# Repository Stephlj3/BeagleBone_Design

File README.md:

# project-template

This repository can be forked for each new project.  This structure has a few goals:
* Standardization of project structure
* Making it trivially easy to distinguish human changes vs. automated outputs
* Tracking hardware bugs and bringup problems in a sensible way

## Description of Folders
* human/   Human modified files.  Many of these will be copies from the bot/ directory with light modification.
  * doc/  Human documentation relevant to the project.
  * input/  The design generator fed in to JITPCB, generated by human.  Also contains a makefile which will populate the bot/ directory.
  * xxxxx/ Copies of folders from the "bot" directory with human modifications.
* bot/ This folder should contain files generated only by a pure pipeline through the tool from the inputspec.
  * esir/ All passes of esir files
  * fab/ gerbers, ncdrill, bom.
  * kicad/ Kicad export.
  
## New Project Process
* Click the 'Use this template' button, set up the repo and clone it.
* Make sure that the stanza.proj file in human/input includes points to the libraries you need (e.g. ocdb)
* Using your (presumably) human brain, write the design generator in human/input.
* Generate your design by running the REPL from the human/input directory
* If JITPCB's outputs do not meet your requirements, copy the outputs from the bot directory (esir, kicad) to the human directory and make modifications in the human directory. 

## Release and Bringup Process
* When you are ready to release a design to fabrication, create a new dated folder in the releases/ dir.  Date format should be YYYYMMDD.
* Make sure all your changes are committed to git.
* Copy the "human" and "bot" folders in to the dated folder in release.
* If you zip a subset of files (eg just the kicad files) to send to the customer or fab house, add the zip file as well in the dated directory.

# Reverse flow usage
When you are finalizing schematics: 
1. Build the generator in the human/input directory, using export-kicad
2. Check the generated schematic file and jitpcb-associations file into the repository
3. Ensure that `export-kicad` is going to use your existing schematic by setting in the list of arguements:
```
  `fresh => false 
```
4. Make changes to the schematic, save them, and check them into the repository
5. When you make a change to the generator, re-run the generator in the input directory. **It will overwrite your kicad project, keeping as many of your saved schematic edits as possible.**
6. If something goes wrong, restore the schematic using git.

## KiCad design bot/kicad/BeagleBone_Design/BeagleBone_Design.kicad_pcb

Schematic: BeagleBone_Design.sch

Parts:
C0, C1, C4, C5, C6, C7, C8, C9, C10, C15, C17, C18, C19, C20, C34, C49, C50, C68, C88, C89, C137, C148: 10.0μF; ipc-two-pin-package$81; Tolerance 0.002%; Maximum Voltage UNKNOWNV
C2: 22.0μF; ipc-two-pin-package$81; Tolerance 0.002%; Maximum Voltage UNKNOWNV
C3, C21, C22, C23, C24, C25, C26, C27, C28, C29, C30, C31, C32, C33, C35, C36, C37, C41, C42, C43, C48, C51, C52, C53, C54, C55, C56, C57, C58, C59, C60, C61, C62, C63, C64, C65, C66, C67, C69, C70, C71, C72, C73, C74, C75, C76, C77, C78, C79, C80, C81, C82, C83, C84, C86, C90, C91, C92, C93, C94, C95, C96, C97, C98, C99, C100, C101, C102, C103, C105, C107, C109, C111, C119, C120, C121, C122, C123, C124, C126, C128, C130, C132, C134, C135, C136, C140, C143, C145, C147, C149, C170, C171: 100.0nF; ipc-two-pin-package$81; Tolerance 0.002%; Maximum Voltage UNKNOWNV
C11, C14, C16, C113: 4.7μF; ipc-two-pin-package$81; Tolerance 0.002%; Maximum Voltage UNKNOWNV
C12, C13, C106, C108, C125, C127, C129, C131, C144: 2.2μF; ipc-two-pin-package$81; Tolerance 0.002%; Maximum Voltage UNKNOWNV
C38, C39, C40, C87, C110, C112, C139: 1.0μF; ipc-two-pin-package$81; Tolerance 0.002%; Maximum Voltage UNKNOWNV
C44, C45, C46: 100.0mF; ipc-two-pin-package$81; Tolerance 0.002%; Maximum Voltage UNKNOWNV
C47: 1.0F; ipc-two-pin-package$81; Tolerance 0.002%; Maximum Voltage UNKNOWNV
C85, C104: 1.0nF; ipc-two-pin-package$81; Tolerance 0.002%; Maximum Voltage UNKNOWNV
C114, C138: 470.0pF; ipc-two-pin-package$81; Tolerance 0.002%; Maximum Voltage UNKNOWNV
C115, C116, C166, C167, C168, C169: 15.0pF; ipc-two-pin-package$81; Tolerance 0.002%; Maximum Voltage UNKNOWNV
C117, C118, C141, C142: 26.0pF; ipc-two-pin-package$81; Tolerance 0.002%; Maximum Voltage UNKNOWNV
C133: 10.0nF; ipc-two-pin-package$81; Tolerance 0.002%; Maximum Voltage UNKNOWNV
C146: 100.0μF; ipc-two-pin-package$81; Tolerance 0.002%; Maximum Voltage UNKNOWNV
C150, C151, C152, C153, C154, C155, C156, C157, C158, C159, C160, C161, C162, C163, C164, C165: 47.0pF; ipc-two-pin-package$81; Tolerance 0.002%; Maximum Voltage UNKNOWNV
D0, D1, D2, D3, D4: LTST-C191TBKT; ipc-two-pin-package$340
D5: RB751V40,115; two-pin-package$403
F0: RXEF010; footprint$62
FB0, FB1, FB2, FB3, FB4, FB5: LI0805H151R-10; ipc-two-pin-package$195
J0: UX60SC-MB-5ST(80); usb_5Ffootprint
J1: 87520-0010BLF; usb-87520-0010BLF-package
J2: PJ-002AH; footprint$53
J3: 10118241-001RLF; hdmi-10118241-001RLF-package
J4: 7499010211A; eth_5Ffootprint
J5: 2201778-1; usd-2201778-1-package
J6, J7: PPPC232LFBN-RC; p46_5Ffootprint
J8: RSM-110-02-S-D; RSM-110-02-S-D_5Ffootprint
J9: 68000-406HLF; _5F68000-406HLF_5Ffootprint
L0, L1, L2: LQM2HPN2R2MG0L; ind_5Ffootprint
Q0, Q1, Q2, Q3: DMN26D0UT-7; SOT-523
R0, R1, R67, R69, R71, R73, R113, R123, R124, R125, R126, R127, R128, R129, R130, R131, R132, R133, R134, R135, R136, R137, R138, R139, R140, R141, R142, R143, R144, R145, R146, R147, R148, R149, R150, R151, R152, R153, R154: 100.0kΩ; ipc-two-pin-package$81; Tolerance 0.02%
R2, R42, R43, R44, R45, R46, R47, R82, R83, R94, R95, R96, R99: 1.5kΩ; ipc-two-pin-package$81; Tolerance 0.02%
R3, R6, R9, R10, R12, R24, R25, R34, R35, R48, R52, R53, R54, R55, R56, R57, R58, R59, R81, R90, R91, R92, R93, R97: 10.0kΩ; ipc-two-pin-package$81; Tolerance 0.02%
R4, R30, R31, R32, R33: 49.9Ω; ipc-two-pin-package$81; Tolerance 0.02%
R5, R26, R37, R38, R39, R40, R49, R50, R60, R62, R63, R65, R76, R77, R78, R79, R89, R98, R111, R112, R117, R118, R119, R120, R121, R122: 0.0Ω; ipc-two-pin-package$81; Tolerance 0.02%
R7, R41, R66, R68, R70, R72, R74, R75, R114, R115, R116: 4.75kΩ; ipc-two-pin-package$81; Tolerance 0.02%
R8: 240.0Ω; ipc-two-pin-package$81; Tolerance 0.02%
R11, R13, R14, R15, R16, R17, R18, R19, R20: 50.0kΩ; ipc-two-pin-package$81; Tolerance 0.02%
R21, R80: 22.0Ω; ipc-two-pin-package$81; Tolerance 0.02%
R22: 280.0kΩ; ipc-two-pin-package$81; Tolerance 0.02%
R23: 470.0kΩ; ipc-two-pin-package$81; Tolerance 0.02%
R27, R28: 470.0Ω; ipc-two-pin-package$81; Tolerance 0.02%
R29: 12.1kΩ; ipc-two-pin-package$81; Tolerance 0.02%
R36: 1.0Ω; ipc-two-pin-package$81; Tolerance 0.02%
R51: 100.0mΩ; ipc-two-pin-package$81; Tolerance 0.02%
R61, R64, R88: 1.0MΩ; ipc-two-pin-package$81; Tolerance 0.02%
R84, R85, R110: 33.0Ω; ipc-two-pin-package$81; Tolerance 0.02%
R86: 27.0kΩ; ipc-two-pin-package$81; Tolerance 0.02%
R87: 10.0Ω; ipc-two-pin-package$81; Tolerance 0.02%
R100, R101, R102, R103, R104, R105, R106, R107, R108, R109, R155: 100.0Ω; ipc-two-pin-package$81; Tolerance 0.02%
S0, S1, S2: KMR231GLFS; footprint$17
U0: TPS65217xxx; qfn-package$74
U1: AM3358BZCZ100; bga-pkg$111
U2: MT41K256M16TW-107 IT:P; bga-pkg$282
U3: MTFC8GAKAJCN-4M-IT; bga-pkg$307
U4: TL5209DR; footprint$12
U5, U6: TPD4S012DRYR; uson-dry0006a
U7: TPS2051D; footprint$40
U8: SN74LVC1G07DCK; dck-R-PDSO-G5
U9: SN74LVC1G06DCK; dck-R-PDSO-G5
U10: SN74LVC2G241DCU; dcu-S-PDSO-G8
U11, U12: TPD4E02B04DQAR; footprint$59
U13: TPD4E05U06QDQARQ1; footprint$65
U14: TDA19988BHN/C1,557; QFN64_5FWITHTHERMALPAD
U15: SN74AUC1G74DCT; sm8-package$406
U16: LAN8710A-EZC-TR; QFN32_5FWITHTHERMALPAD
U17: 24LC32AT-I/OT; SOT-23-5-package
Y0: CM200C32768AZFT; xtal_5Ffootprint
Y1: 445C33D24M00000; SMD-2$350
Y2: ASDMB-24.576MHZ-LC-T; SDMB-24-576MHZ-package
Y3: 445C33D25M00000; SMD-2$350

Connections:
AIN0: J7.39, U1.B6 (ain0)
AIN1: J7.40, U1.C7 (ain1)
AIN2: J7.37, U1.B7 (ain2)
AIN3: J7.38, U1.A7 (ain3)
AIN4: J7.33, U1.C8 (ain4)
AIN5: J7.36, U1.B8 (ain5)
AIN6: J7.35, U1.A8 (ain6)
AIN7: R74.2, R75.2, U1.C9 (ain7)
BF_IN: U1.R14 (io36), U9.2 (a)
B_UART0_RX: J9.4, R113.2, U10.2 (a1)
B_UART0_TX: J9.5, U10.3 (y2)
CLKOUT2: J7.41, J8.18, R119.2, R120.2
CLKOUT_SRC: R119.1, U1.D14 (io1)
CPU_vdd_pll: C44.1, C45.1, C46.1, C47.1, FB0.2, U1.E7 (VDDS_PLL_DDR), U1.H15 (VDDS_PLL_MPU), U1.R10 (VDDS_PLL_CORE_LCD), U1.R11 (VDDS_OSC)
DDR3L_ZQ: R8.1, U2.L8 (pwr_zq)
DDR_A0: U1.F3 (acc_a0), U2.N3 (acc_a0)
DDR_A1: U1.H1 (acc_a1), U2.P7 (acc_a1)
DDR_A2: U1.E4 (acc_a2), U2.P3 (acc_a2)
DDR_A3: U1.C3 (acc_a3), U2.N2 (acc_a3)
DDR_A4: U1.C2 (acc_a4), U2.P8 (acc_a4)
DDR_A5: U1.B1 (acc_a5), U2.P2 (acc_a5)
DDR_A6: U1.D5 (acc_a6), U2.R8 (acc_a6)
DDR_A7: U1.E2 (acc_a7), U2.R2 (acc_a7)
DDR_A8: U1.D4 (acc_a8), U2.T8 (acc_a8)
DDR_A9: U1.C1 (acc_a9), U2.R3 (acc_a9)
DDR_A10: U1.F4 (acc_a10), U2.L7 (acc_a10)
DDR_A11: U1.F2 (acc_a11), U2.R7 (acc_a11)
DDR_A12: U1.E3 (acc_a12), U2.N7 (acc_a12)
DDR_A13: U1.H3 (acc_a13), U2.T3 (acc_a13)
DDR_A14: U1.H4 (acc_a14), U2.T7 (acc_a14)
DDR_BA0: U1.C4 (acc_ba0), U2.M2 (acc_ba0)
DDR_BA1: U1.E1 (acc_ba1), U2.N8 (acc_ba1)
DDR_BA2: U1.B3 (acc_ba2), U2.M3 (acc_ba2)
DDR_CASn: U1.F1 (acc_nCAS), U2.K3 (acc_nCAS)
DDR_CKE: R3.1, U1.G3 (acc_cke), U2.K9 (acc_cke)
DDR_CLK: U1.D2 (acc_ck_P), U2.J7 (acc_ck_P)
DDR_CLKn: U1.D1 (acc_ck_N), U2.K7 (acc_ck_N)
DDR_CSn: U1.H2 (acc_nCS), U2.L2 (acc_nCS)
DDR_D0: U1.M3 (dat_dq0), U2.E3 (dat_dq0)
DDR_D1: U1.M4 (dat_dq1), U2.F7 (dat_dq1)
DDR_D2: U1.N1 (dat_dq2), U2.F2 (dat_dq2)
DDR_D3: U1.N2 (dat_dq3), U2.F8 (dat_dq3)
DDR_D4: U1.N3 (dat_dq4), U2.H3 (dat_dq4)
DDR_D5: U1.N4 (dat_dq5), U2.H8 (dat_dq5)
DDR_D6: U1.P3 (dat_dq6), U2.G2 (dat_dq6)
DDR_D7: U1.P4 (dat_dq7), U2.H7 (dat_dq7)
DDR_D8: U1.J1 (dat_dq8), U2.D7 (dat_dq8)
DDR_D9: U1.K1 (dat_dq9), U2.C3 (dat_dq9)
DDR_D10: U1.K2 (dat_dq10), U2.C8 (dat_dq10)
DDR_D11: U1.K3 (dat_dq11), U2.C2 (dat_dq11)
DDR_D12: U1.K4 (dat_dq12), U2.A7 (dat_dq12)
DDR_D13: U1.L3 (dat_dq13), U2.A2 (dat_dq13)
DDR_D14: U1.L4 (dat_dq14), U2.B8 (dat_dq14)
DDR_D15: U1.M1 (dat_dq15), U2.A3 (dat_dq15)
DDR_DQM0: U1.M2 (dat_dm0), U2.E7 (dat_dm0)
DDR_DQM1: U1.J2 (dat_dm1), U2.D3 (dat_dm1)
DDR_DQS0: U1.P1 (dat_dqs0_P), U2.F3 (dat_dqs0_P)
DDR_DQS1: U1.L1 (dat_dqs1_P), U2.C7 (dat_dqs1_P)
DDR_DQSN0: U1.P2 (dat_dqs0_N), U2.G3 (dat_dqs0_N)
DDR_DQSN1: U1.L2 (dat_dqs1_N), U2.B7 (dat_dqs1_N)
DDR_ODT: U1.G1 (acc_odt), U2.K1 (acc_odt)
DDR_RASn: U1.G4 (acc_nRAS), U2.J3 (acc_nRAS)
DDR_RESETn: R2.1, U1.G2 (acc_nRESET), U2.T2 (acc_nRESET)
DDR_VREF: C57.1, C104.1, C105.1, R9.2, R10.1, U1.J4 (DDR_VREF), U2.H1 (pwr_vrefdq), U2.M8 (pwr_vrefca)
DDR_WEn: U1.B2 (acc_nWE), U2.L3 (acc_nWE)
DVI_+5V: F0.1, J3.19 (vcc_5v), R82.2, R83.2
EARTH_GND: J0.6 (shield1), J0.7 (shield2), J0.8 (shield3), J0.9 (shield4), J1.5 (shield1), J1.6 (shield2), J3.20 (mtg1), J3.21 (mtg2), J3.22 (mtg3), J3.23 (mtg4), J4.15 (shield1), J4.16 (shield2), J5.11 (gnd1), J5.12 (gnd2), J5.13 (gnd3), J5.14 (gnd4), J5.15 (gnd5), J5.16 (gnd6), R36.1
EHRPWM1A: J7.14, U1.U14 (io34)
EHRPWM1B: J7.16, U1.T14 (io35)
EHRPWM2A: J6.19, U1.U10 (io24)
EHRPWM2B: J6.13, U1.T10 (io25)
ETH_TXD4: R97.1, U16.18 (nINT_TXER_TXD4)
FF_Q: R85.1, U15.5 (q)
GNDA_ADC: C82.2, C83.2, C84.2, C85.2, FB2.2, J7.34, U1.A9 (VREFN), U1.E8 (VSSA_ADC)
GND_OSC0: C117.2, C118.2, R62.1, R65.2, U1.V11 (VSS_OSC)
GND_OSC1: C115.2, C116.2, R65.1, U1.A5 (VSS_RTC)
GPIO0_7: J7.42, R121.2, R122.2
GPIO0_7SRC: R121.1, U1.C18 (io67)
GPIO0_26: J6.14, U1.T11 (io26)
GPIO0_27: J6.17, U1.U12 (io27)
GPIO1_12: J6.12, U1.T12 (io28)
GPIO1_13: J6.11, U1.R12 (io29)
GPIO1_14: J6.16, U1.V13 (io30)
GPIO1_15: J6.15, U1.U13 (io31)
GPIO1_16: J7.15, R117.2, R118.2
GPIO1_17: J7.23, U1.V14 (io33)
GPIO1_28: J7.12, U1.U18 (io13)
GPIO1_29: J6.26, U1.V6 (io5)
GPIO2_1: J6.18, U1.V12 (io4)
GPIO3_18: R122.1, U1.B12 (io111)
GPIO3_19: J7.27, U1.C13 (io112)
GPIO3_20: R120.1, U1.D13 (io113)
GPIO3_21: J7.25, R84.2, U1.A14 (io106)
GRNA: J4.9 (grna), U16.3 (LED1_REGOFF)
HDMICLK_DISn: U1.V17 (io43)
HDMI_1V8: C124.1, C125.1, C126.1, C127.1, C128.1, C129.1, C130.1, C131.1, FB4.2, U14.5 (VDDC0-1V8), U14.14 (VDDIOA-1V8), U14.29 (VDDC1-1V8), U14.35 (VDDA0-1V8), U14.36 (VDDA1-TX-1V8), U14.41 (VDDA2-TX-1V8), U14.46 (VDDA3-TX-1V8), U14.47 (VDDA-PLL0-1V8), U14.48 (VDDA-PLL1-1V8), U14.55 (VDDIOB-1V8)
HDMI_12MHZ: R85.2, U14.27 (OSC_IN_AP3)
HDMI_CEC: D5.1 (c), J3.15 (cec), U13.4 (IO3), U14.30 (CEC)
HDMI_DSCL: J3.17 (scl), R82.1, U13.1 (IO1), U14.33 (DSCL)
HDMI_DSDA: J3.18 (sda), R83.1, U13.2 (IO2), U14.32 (DSDA)
HDMI_HPD: J3.1 (hplg), U13.5 (IO4), U14.31 (HPD)
HDMI_INT: R81.1, U1.U16 (io41), U14.50 (INT)
HDMI_TX0_N: J3.11 (dat0_n), U12.1 (IO1), U14.39 (TX0_N)
HDMI_TX0_P: J3.9 (dat0_p), U12.2 (IO2), U14.40 (TX0_P)
HDMI_TX1_N: J3.8 (dat1_n), U11.4 (IO3), U14.42 (TX1_N)
HDMI_TX1_P: J3.6 (dat1_p), U11.5 (IO4), U14.43 (TX1_P)
HDMI_TX2_N: J3.5 (dat2_n), U11.1 (IO1), U14.44 (TX2_N)
HDMI_TX2_P: J3.3 (dat2_p), U11.2 (IO2), U14.45 (TX2_P)
HDMI_TXC_N: J3.14 (clk_n), U12.4 (IO3), U14.37 (TXC_N)
HDMI_TXC_P: J3.12 (clk_p), U12.5 (IO4), U14.38 (TXC_P)
I2C0_SCL: R42.1, U0.28 (SCL), U1.C16 (io63), U14.52 (CSCL), U17.1 (scl)
I2C0_SDA: R43.1, U0.27 (SDA), U1.C17 (io64), U14.51 (CSDA), U17.3 (sda)
I2C1_SCL: J7.17, R44.1, U1.A16 (io53)
I2C1_SDA: J7.18, R45.1, U1.B16 (io52)
I2C2_SCL: J7.19, R46.1, U1.D17 (io62)
I2C2_SDA: J7.20, R47.1, U1.D18 (io61)
JTAG_EMU0: J8.13, R114.2, U1.C14 (io2)
JTAG_EMU1: J8.14, R116.2, U1.B14 (io3)
JTAG_TCK: J8.9, J8.11, U1.A12 (tck)
JTAG_TDI: J8.3, U1.B11 (tdi)
JTAG_TDO: J8.7, U1.A11 (tdo)
JTAG_TMS: J8.1, U1.C11 (tms)
JTAG_TRSTn: J8.2, R115.2, U1.B10 (ntrst)
LCDDE: R79.2, U1.R6 (io105)
LCDHSYNC: R78.2, U1.R5 (io104)
LCDPCLK: R80.2, U1.V5 (io102)
LCDVSYNC: R77.2, U1.U5 (io103)
LCD_DATA0: C150.1, J6.45, R133.1, R134.1, U1.R1 (io86), U14.15 (VPC3)
LCD_DATA1: C151.1, J6.46, R135.1, R136.1, U1.R2 (io87), U14.13 (VPC4)
LCD_DATA2: C152.1, J6.43, R123.1, R124.1, R155.1, U1.R3 (io88), U14.12 (VPC5)
LCD_DATA3: C153.1, J6.44, R125.1, R126.1, U1.R4 (io89), U14.11 (VPC6)
LCD_DATA4: C154.1, J6.41, R127.1, R128.1, U1.T1 (io90), U14.10 (VPC7)
LCD_DATA5: C155.1, J6.42, R129.1, R130.1, U1.T2 (io91), U14.7 (VPB2)
LCD_DATA6: C156.1, J6.39, R137.1, R138.1, U1.T3 (io92), U14.6 (VPB3)
LCD_DATA7: C157.1, J6.40, R139.1, R140.1, U1.T4 (io93), U14.3 (VPB4)
LCD_DATA8: C158.1, J6.37, R141.1, R142.1, U1.U1 (io94), U14.2 (VPB5)
LCD_DATA9: C159.1, J6.38, R143.1, R144.1, U1.U2 (io95), U14.1 (VPB6)
LCD_DATA10: C160.1, J6.36, R145.1, R146.1, U1.U3 (io96), U14.64 (VPB7)
LCD_DATA11: C161.1, J6.34, R147.1, R148.1, U1.U4 (io97), U14.60 (VPA3)
LCD_DATA12: C162.1, J6.35, R149.1, R150.1, U1.V2 (io98), U14.59 (VPA4)
LCD_DATA13: C163.1, J6.33, R151.1, R152.1, U1.V3 (io99), U14.58 (VPA5)
LCD_DATA14: C164.1, J6.31, R131.1, R132.1, U1.V4 (io100), U14.57 (VPA6)
LCD_DATA15: C165.1, J6.32, R153.1, R154.1, U1.T5 (io101), U14.56 (VPA7)
LCD_DE: J6.30, R79.1, U14.20 (DE-VREF)
LCD_HSYNC: J6.29, R78.1, U14.22 (HSYNC-VREF)
LCD_PCLK: J6.28, R80.1, U14.4 (PCLK)
LCD_VSYNC: J6.27, R77.1, U14.21 (VSYNC-VREF)
LDO_PGOOD: U0.46 (LDO_PGOOD), U1.B5 (RTC_PORZn)
LEDAA: D1.1 (a), R66.2
LEDBA: D2.1 (a), R68.2
LEDCA: D3.1 (a), R70.2
LEDDA: D4.1 (a), R72.2
LOOP_12M: U15.2 (d), U15.3 (qn)
MDIO_CLK: U1.M18 (io84), U16.17 (MDC)
MDIO_DATA: R99.2, U1.M17 (io85), U16.16 (MDIO)
MII1_COL: R108.1, U1.H16 (io75)
MII1_CRS_DV: R109.1, U1.H17 (io74)
MII1_REFCLK: R110.2, R111.1, R112.1
MII1_RXCLK: R105.1, U1.L18 (io76)
MII1_RXD0: R103.1, U1.M16 (io77)
MII1_RXD1: R102.1, U1.L15 (io78)
MII1_RXD2: R101.1, U1.L16 (io79)
MII1_RXD3: R100.1, U1.L17 (io80)
MII1_RXDV: R104.1, U1.J17 (io82)
MII1_RXERR: R106.1, U1.J15 (io81)
MII1_TXCLK: R107.1, U1.K18 (io68)
MII1_TXD0: U1.K17 (io69)
MII1_TXD1: U1.K16 (io70)
MII1_TXD2: U1.K15 (io71)
MII1_TXD3: U1.J18 (io72)
MII1_TXEN: U1.J16 (io73)
MMC0_CD: J5.9 (swa), J8.19, R53.2, U1.C15 (io54)
MMC0_CLKO: J5.5 (clk), R59.2, U1.G17 (io44)
MMC0_CMD: J5.3 (cmd), R58.2, U1.G18 (io45)
MMC0_DAT0: J5.7 (dat0), R54.2, U1.G16 (io46)
MMC0_DAT1: J5.8 (dat1), R55.2, U1.G15 (io47)
MMC0_DAT2: J5.1 (dat2), R56.2, U1.F18 (io48)
MMC0_DAT3: J5.2 (cd_dat3), R57.2, U1.F17 (io49)
MMC1_CLK: J6.21, R21.1, U1.U9 (io6)
MMC1_CMD: J6.20, R12.2, U1.V9 (io7), U3.M5 (dat_cmd)
MMC1_DAT0: J6.25, R13.2, U1.U7 (io16), U3.A3 (dat_d0)
MMC1_DAT1: J6.24, R14.2, U1.V7 (io17), U3.A4 (dat_d1)
MMC1_DAT2: J6.5, R15.2, U1.R8 (io18), U3.A5 (dat_d2)
MMC1_DAT3: J6.6, R16.2, U1.T8 (io19), U3.B2 (dat_d3)
MMC1_DAT4: J6.23, R17.2, U1.U8 (io20), U3.B3 (dat_d4)
MMC1_DAT5: J6.22, R18.2, U1.V8 (io21), U3.B4 (dat_d5)
MMC1_DAT6: J6.3, R19.2, U1.R9 (io22), U3.B5 (dat_d6)
MMC1_DAT7: J6.4, R20.2, U1.T9 (io23), U3.B6 (dat_d7)
MODE2: R94.1, R108.2, U16.15 (COL_CRS_DV_MODE2)
OSC0_IN: C117.1, R61.1, U1.V10 (OSC0_IN), Y1.1 (xtal1)
OSC0_OUT: R60.2, R61.2, U1.U11 (OSC0_OUT)
OSC1_IN: C115.1, R64.1, U1.A6 (OSC1_IN), Y0.1 (xtal1)
OSC1_OUT: R63.2, R64.2, U1.A4 (OSC1_OUT)
PHYX: C142.1, R87.1, Y3.2 (xtal2)
PHY_XTAL1: C141.1, R88.1, R89.1, Y3.1 (xtal1)
PHY_XTAL2: R87.2, R88.2, U16.4 (XTAL2)
PMIC_INT: R1.1, U0.45 (INT), U1.B18 (NNMI)
PMIC_ISET1: U0.35 (ISET1)
PMIC_ISET2: U0.36 (ISET2)
PMIC_PGOOD: U0.26 (PGOOD), U1.B15 (PORZn), U8.2 (a)
PMIC_POWR_EN: U0.9 (PWR_EN), U1.C6 (PMIC_POWER_EN)
PMIC_bypass: C4.1, U0.47 (BYPASS)
PMIC_int_ldo: C3.1, U0.48 (INT_LDO)
PMIC_sw1: L0.1, U0.20 (L1)
PMIC_sw2: L1.1, U0.23 (L2)
PMIC_sw3: L2.1, U0.31 (L3)
PROC_A15: U1.A15 (io0)
PWR_BUT: J7.9, S0.1 (p1), S0.3 (p3), U0.25 (PB_IN)
PWR_LEDR: D0.2 (c), R41.1
RCLKIN: R89.2, R112.2, U16.5 (XTAL1_CLKIN)
REFCLK0: R90.1, R105.2, R111.2, U16.7 (RXCLK_PHYAD1)
RXD0_MODE0: R96.1, R103.2, U16.11 (RXD0_MODE0)
RXD1_MODE1: R95.1, R102.2, U16.10 (RXD1_MODE1)
RXN: C169.1, J4.6 (rd_n), R33.1, U16.30 (RXN)
RXP: C168.1, J4.3 (rd_p), R32.1, U16.31 (RXP)
SDBOOT: R155.2, S2.1 (p1), S2.3 (p3)
SPI1_CS0: J7.28, U1.C12 (io110), U14.25 (AP1)
SPI1_D0: J7.29, U1.B13 (io108), U14.24 (AP0)
SPI1_D1: J7.30, U1.D12 (io109)
SPI1_SCLK: J7.31, U1.A13 (io107), U14.23 (ACLK)
SYS_5V: C2.1, C5.1, C7.1, C9.1, C11.1, C14.1, C16.1, C112.1, C119.1, C146.1, F0.2, J7.7, J7.8, R66.1, R68.1, R70.1, R72.1, U0.2 (VINLDO), U0.7 (SYS1), U0.8 (SYS2), U0.21 (VIN_DCDC1), U0.22 (VIN_DCDC2), U0.32 (VIN_DCDC3), U0.39 (LDO3_IN), U0.42 (LDO4_IN), U4.2 (IN), U7.2 (in1), U7.3 (in2)
SYS_RESETn: C144.1, C171.2, J7.10, J8.15, R48.1, S1.1 (p1), S1.3 (p3), U1.A10 (NRESET_INOUT), U8.4 (y), U16.19 (nRST)
TCT_RCT: C134.1, J4.4 (tct), J4.5 (rct), R98.1
TIMER4: J6.7, U1.R7 (io11)
TIMER5: J6.9, U1.T6 (io12)
TIMER6: J6.10, U1.U6 (io9)
TIMER7: J6.8, U1.T7 (io10)
TXN: C167.1, J4.2 (td_n), R31.1, U16.28 (TXN)
TXP: C166.1, J4.1 (td_p), R30.1, U16.29 (TXP)
U5_H18: R110.1, U1.H18 (io83)
U5_R13: R118.1, U1.R13 (io32)
U5_T13: R117.1, U1.T13 (io8)
UART0_RX: U1.E15 (io56), U10.6 (y1)
UART0_TX: U1.E16 (io55), U10.5 (a2)
UART1_RXD: J7.26, U1.D16 (io60)
UART1_TXD: J7.24, U1.D15 (io59)
UART2_RXD: J7.22, U1.A17 (io50)
UART2_TXD: J7.21, U1.B17 (io51)
UART4_RXD: J7.11, U1.T17 (io14)
UART4_TXD: J7.13, U1.U17 (io15)
USB0_DM: J0.2 (dm), U1.N18 (usb0_data_N), U5.2 (DM)
USB0_DP: J0.3 (dp), U1.N17 (usb0_data_P), U5.1 (DP)
USB0_ID: J0.4 (id), U1.P16 (USB0_ID), U5.3 (ID)
USB1_DM: J1.2 (dm), U1.R18 (usb1_data_N), U6.2 (DM)
USB1_DP: J1.3 (dp), U1.R17 (usb1_data_P), U6.1 (DP)
USB1_DRVVBUS: R52.1, U1.F15 (io66), U7.4 (en)
USB1_ID: R50.1, U1.P17 (USB1_ID)
USB1_OCn: R24.1, U1.T16 (io42), U7.5 (oc)
USB1_PWR: C120.1, C147.1, FB3.1, R51.2, U6.6 (VBUS), U7.6 (out3), U7.7 (out2), U7.8 (out1)
USB1_VBUS: R51.1, U1.T18 (USB1_VBUS)
USB_DC: C1.1, C145.1, J0.1 (vdd), R49.1, U0.12 (USB), U5.6 (VBUS)
USR0: Q0.2 (gate), R67.1, U1.V15 (io37)
USR1: Q1.2 (gate), R69.1, U1.U15 (io38)
USR2: Q2.2 (gate), R71.1, U1.T15 (io39)
USR3: Q3.2 (gate), R73.1, U1.V16 (io40)
VBUS: FB3.2, J1.1 (vbus)
VDDS: C77.1, C78.1, C79.1, C80.1, C81.1, R37.2, U1.E6 (VDDS1), U1.E14 (VDDS2), U1.F9 (VDDS3), U1.K13 (VDDS4), U1.N6 (VDDS5), U1.P9 (VDDS6), U1.P14 (VDDS7)
VDDS_DDR: C49.1, C50.1, C51.1, C52.1, C53.1, C54.1, C55.1, C56.1, C88.1, C89.1, C90.1, C91.1, C92.1, C93.1, C94.1, C95.1, C96.1, C97.1, C98.1, C99.1, C100.1, C101.1, C102.1, C103.1, R2.2, R9.1, R40.2, U1.E5 (VDDS_DDR1), U1.F5 (VDDS_DDR2), U1.G5 (VDDS_DDR3), U1.H5 (VDDS_DDR4), U1.J5 (VDDS_DDR5), U1.K5 (VDDS_DDR6), U1.L5 (VDDS_DDR7), U2.A1 (pwr_vddq0), U2.A8 (pwr_vddq5), U2.B2 (pwr_vdd2), U2.C1 (pwr_vddq1), U2.C9 (pwr_vddq6), U2.D2 (pwr_vddq3), U2.D9 (pwr_vdd6), U2.E9 (pwr_vddq7), U2.F1 (pwr_vddq2), U2.G7 (pwr_vdd4), U2.H2 (pwr_vddq4), U2.H9 (pwr_vddq8), U2.K2 (pwr_vdd3), U2.K8 (pwr_vdd5), U2.N1 (pwr_vdd0), U2.N9 (pwr_vdd7), U2.R1 (pwr_vdd1), U2.R9 (pwr_vdd8)
VDD_1V8: C15.1, C41.1, C42.1, C43.1, FB0.1, FB1.1, FB4.1, U0.40 (LDO3), U1.D10 (VDDS_SRAM_MPU_BB), U1.E9 (VDDS_SRAM_CORE_BG), U1.N16 (VDDA1P8V_USB0), U1.R16 (VDDA1P8V_USB1)
VDD_3V3A: C17.1, C48.1, C58.1, C59.1, C60.1, C61.1, C62.1, C63.1, C64.1, C65.1, C66.1, C67.1, C68.1, C69.1, C70.1, C71.1, C72.1, C73.1, C74.1, C75.1, C76.1, C122.1, C132.1, C133.1, C143.1, R24.2, R35.1, R42.2, R43.2, R44.2, R45.2, R46.2, R47.2, R48.2, R124.2, R126.2, R128.2, R130.2, R132.2, R134.2, R136.2, R138.2, R140.2, R142.2, R144.2, R146.2, R148.2, R150.2, R152.2, R154.2, U0.43 (LDO4), U1.E10 (VDDSHV61), U1.E11 (VDDSHV62), U1.E12 (VDDSHV63), U1.E13 (VDDSHV64), U1.F14 (VDDSHV65), U1.G14 (VDDSHV66), U1.H14 (VDDSHV41), U1.J14 (VDDSHV42), U1.K14 (VDDSHV51), U1.L14 (VDDSHV52), U1.N5 (VDDSHV67), U1.N15 (VDDA3P3V_USB0), U1.P5 (VDDSHV68), U1.P6 (VDDSHV69), U1.P7 (VDDSHV11), U1.P8 (VDDSHV12), U1.P10 (VDDSHV21), U1.P11 (VDDSHV22), U1.P12 (VDDSHV31), U1.P13 (VDDSHV32), U1.R15 (VDDA3P3V_USB1), U4.1 (EN), U9.5 (vcc), U15.6 (clrn), U15.7 (pren), U15.8 (vcc), U17.4 (vcc), Y2.4 (vdd)
VDD_3V3AUX: C13.1, D0.1 (a), U0.1 (VLDO2)
VDD_3V3B: C106.1, C107.1, C108.1, C109.1, C113.1, C123.1, C140.1, C148.1, C149.1, C170.2, FB5.1, J5.4 (vdd), J7.3, J7.4, J8.5, R11.1, R12.1, R13.1, R14.1, R15.1, R16.1, R17.1, R18.1, R19.1, R20.1, R22.1, R53.1, R54.1, R55.1, R56.1, R57.1, R58.1, R59.1, R74.1, R81.2, R86.1, R94.2, R95.2, R96.2, R99.1, R114.1, R116.1, U3.C6 (pwr_vccq0), U3.E6 (pwr_vcc0), U3.F5 (pwr_vcc1), U3.J10 (pwr_vcc2), U3.K9 (pwr_vcc3), U3.M4 (pwr_vccq1), U3.N4 (pwr_vccq2), U3.P3 (pwr_vccq3), U3.P5 (pwr_vccq4), U4.3 (OUT), U10.7 (oe_2), U10.8 (vcc), U16.12 (VDDIO)
VDD_5V: C0.1, J2.1 (VDD), J7.5, J7.6, U0.10 (AC)
VDD_ADC: C82.1, FB1.2, J7.32, R5.1, U1.D8 (VDDA_ADC)
VDD_CORE: C10.1, C18.1, C19.1, C20.1, C21.1, C22.1, C23.1, C24.1, C25.1, C26.1, C27.1, C28.1, C29.1, C30.1, C31.1, C32.1, C33.1, L2.2, U0.29 (VDCDC3), U1.F6 (VDD_CORE1), U1.F7 (VDD_CORE2), U1.G6 (VDD_CORE3), U1.G7 (VDD_CORE4), U1.G10 (VDD_CORE5), U1.H11 (VDD_CORE6), U1.J12 (VDD_CORE7), U1.K6 (VDD_CORE8), U1.K8 (VDD_CORE9), U1.K12 (VDD_CORE10), U1.L6 (VDD_CORE11), U1.L7 (VDD_CORE12), U1.L8 (VDD_CORE13), U1.L9 (VDD_CORE14), U1.M11 (VDD_CORE15), U1.M13 (VDD_CORE16), U1.N8 (VDD_CORE17), U1.N9 (VDD_CORE18), U1.N12 (VDD_CORE19), U1.N13 (VDD_CORE20)
VDD_MPU: C8.1, C34.1, C35.1, C36.1, C37.1, L1.2, U0.24 (VDCDC2), U1.F10 (VDD_MPU1), U1.F11 (VDD_MPU2), U1.F12 (VDD_MPU3), U1.F13 (VDD_MPU4), U1.G13 (VDD_MPU5), U1.H13 (VDD_MPU6), U1.J13 (VDD_MPU7)
VDD_PHYA: C135.1, C136.1, C137.1, FB5.2, R30.2, R31.2, R32.2, R33.2, R98.2, U16.1 (VDD2A), U16.27 (VDD1A)
VIO: C121.1, R0.2, R1.2, R39.2, U0.18 (VIO), U8.5 (vcc)
VRTC: C86.1, R7.2, R38.2, U1.D7 (VDDS_RTC)
WAKEUP: R0.1, R7.1, U0.13 (WAKEUP), U1.C5 (EXT_WAKEUP)
XDMA_EVENT_INTRO: J8.17, U15.1 (clk)
XTAL0_OUT: C118.1, R60.1, Y1.2 (xtal2)
XTAL1_OUT: C116.1, R63.1, Y0.4 (xtal2)
Y4_CLK: R84.1, Y2.3 (output)
YELA: J4.12 (yela), R34.1, U16.2 (LED2_nINTSEL)
eMMC_RSTn: R11.2, R76.1, U3.K5 (nRESET)
net_BUFFER_Y: R76.2, U9.4 (y)
net_CPU_USB0_CE: U1.M15 (USB0_CE)
net_CPU_USB0_VBUS: R49.2, U1.P15 (USB0_VBUS)
net_CPU_USB1_CE: U1.P18 (USB1_CE)
net_CPU_cpu_CAP_VBB_MPU: C40.1, U1.C10 (CAP_VBB_MPU)
net_CPU_cpu_CAP_VDD_RTC: C87.1, U1.D6 (CAP_VDD_RTC)
net_CPU_cpu_CAP_VDD_SRAM_CORE: C38.1, U1.D9 (CAP_VDD_SRAM_CORE)
net_CPU_cpu_CAP_VDD_SRAM_MPU: C39.1, U1.D11 (CAP_VDD_SRAM_MPU)
net_CPU_cpu_DDR_VTP: R4.1, U1.J3 (DDR_VTP)
net_CPU_cpu_ENZ_KALDO_1P8V: R6.1, U1.B4 (ENZ_KALDO_1P8V)
net_CPU_cpu_VREFP: C83.1, C84.1, C85.1, R5.2, U1.B9 (VREFP)
net_CPU_vdd_mpuon: U1.A2 (VDD_MPU_MON)
net_D6_a: D5.2 (a), R86.2
net_EEPROM_WP: R35.2, U17.5 (wp)
net_ETH_CONN_GRN_C: J4.10 (grnc), R28.1
net_ETH_CONN_YEL_C: J4.11 (yelc), R27.1
net_ETH_TRANS_CRS: R109.2, U16.14 (CRS)
net_ETH_TRANS_RBIAS: R29.1, U16.32 (RBIAS)
net_ETH_TRANS_RXD2_RMIISEL: R91.1, R101.2, U16.9 (RXD2_RMIISEL)
net_ETH_TRANS_RXD3_PHYAD2: R92.1, R100.2, U16.8 (RXD3_PHYAD2)
net_ETH_TRANS_RXDV: R104.2, U16.26 (RXDV)
net_ETH_TRANS_RXER_RXD4_PHYAD0: R93.1, R106.2, U16.13 (RXER_RXD4_PHYAD0)
net_ETH_TRANS_TXCLK: R107.2, U16.20 (TXCLK)
net_ETH_TRANS_TXD0: U16.22 (TXD0)
net_ETH_TRANS_TXD1: U16.23 (TXD1)
net_ETH_TRANS_TXD2: U16.24 (TXD2)
net_ETH_TRANS_TXD3: U16.25 (TXD3)
net_ETH_TRANS_TXEN: U16.21 (TXEN)
net_ETH_TRANS_VDDCR: C138.1, C139.1, U16.6 (VDDCR)
net_HDMI_TRANS_AP2: U14.26 (AP2)
net_HDMI_TRANS_AP4: U14.28 (AP4)
net_HDMI_TRANS_SWING: R25.1, U14.34 (EXT_SWING)
net_HDMI_TRANS_TEST: R26.1, U14.49 (TEST)
net_LDO_FB: C114.1, R22.2, R23.1, U4.4 (ADJ/BYP)
net_PMIC_BATT: U0.4 (BAT1), U0.5 (BAT2), U0.6 (BAT_SENSE)
net_PMIC_ISINK1: U0.34 (ISINK1)
net_PMIC_ISINK2: U0.33 (ISINK2)
net_PMIC_MUX_IN: U0.14 (MUX_IN)
net_PMIC_MUX_OUT: U0.16 (MUX_OUT)
net_PMIC_RESET: U0.44 (RESET)
net_PMIC_TS: U0.11 (TS)
net_PMIC_VOUT_DCDC1: C6.1, L0.2, R40.1, U0.19 (VDCDC1)
net_PMIC_VOUT_LDO1: C12.1, R37.1, R38.1, R39.1, U0.3 (VLDO1)
net_Y4_OE: Y2.1 (standby)
net_eMMC_eMMC_VDDIM: C110.1, C111.1, U3.C2 (VDDIM)
net_eMMC_eMMC_dat_clk: R21.2, U3.M6 (dat_clk)

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
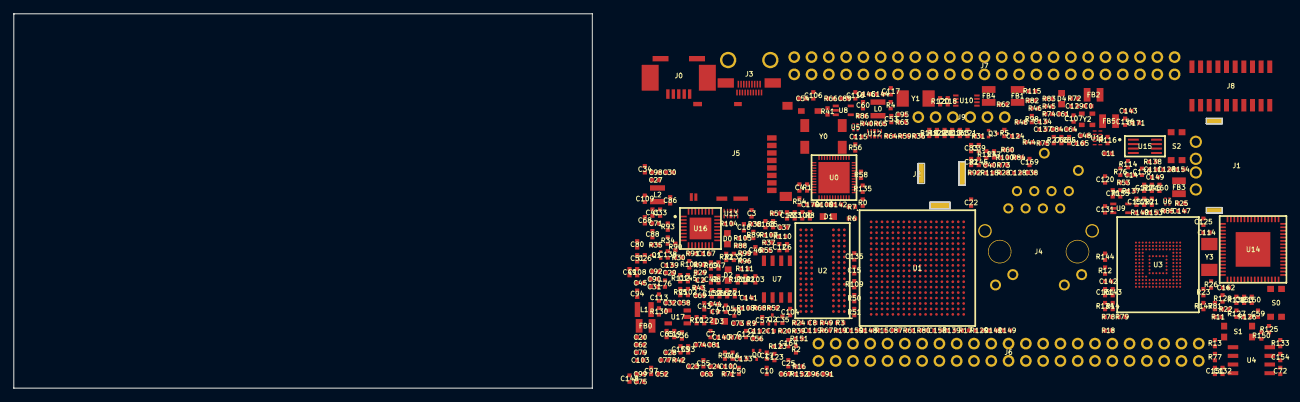
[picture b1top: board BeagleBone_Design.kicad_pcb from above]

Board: 4 copper layers, 177.5 x 55.0 mm, 381 parts (0 on the bottom side), 300 nets, no tracks yet.

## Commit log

2020-07-25 first draft of BeagleBone_Design in new project template
2020-07-30 Beagle Design update after review
2020-07-31 clean up Beagle schematic
